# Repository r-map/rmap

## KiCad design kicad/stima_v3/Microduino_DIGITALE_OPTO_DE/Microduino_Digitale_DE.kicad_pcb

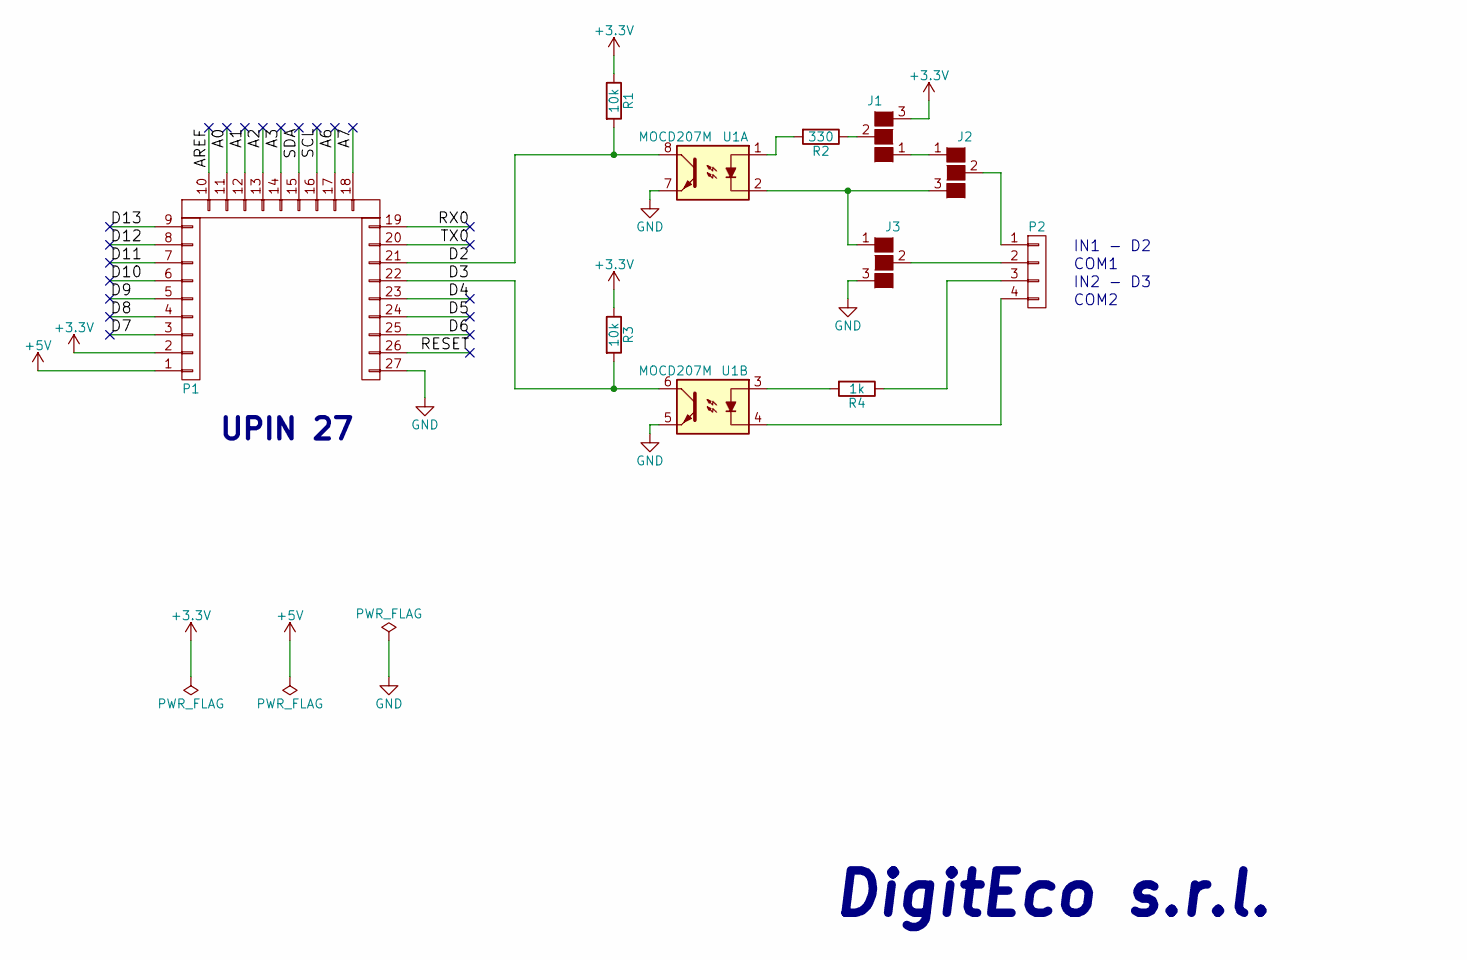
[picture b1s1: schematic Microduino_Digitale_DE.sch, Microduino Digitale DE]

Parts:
J1, J2, J3: GS3
P1: CONN_1x27; Upin_27
P2: CONN_01X04; WHURT_4pin_90°_61900411021
R1, R3: 10k; R_0805
R2: 330; R_0805
R4: 1k; R_0805
U1: MOCD207M; SOIC-8_3.9x4.9mm_Pitch1.27mm

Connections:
+3V3: J1.3 (G3), P1.2, R1.1, R3.1
+5V: P1.1
/A0: P1.11
/A1: P1.12
/A2: P1.13
/A3: P1.14
/A6: P1.17
/A7: P1.18
/AREF: P1.10
/D2: P1.21, R1.2, U1.8
/D3: P1.22, R3.2, U1.6
/D4: P1.23
/D5: P1.24
/D6: P1.25
/D7: P1.3
/D8: P1.4
/D9: P1.5
/D10: P1.6
/D11: P1.7
/D12: P1.8
/D13: P1.9
/RESET: P1.26
/RX0: P1.19
/SCL: P1.16
/SDA: P1.15
/TX0: P1.20
GND: J3.3 (G3), P1.27, U1.5, U1.7
unnamed: J1.1 (G1), J2.1 (G1)
unnamed: J1.2 (G2), R2.1
unnamed: J2.2 (G2), P2.1
unnamed: J2.3 (G3), J3.1 (G1), U1.2
unnamed: J3.2 (G2), P2.2
unnamed: P2.3, R4.1
unnamed: P2.4, U1.4
unnamed: R2.2, U1.1
unnamed: R4.2, U1.3

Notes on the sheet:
UPIN 27
DigitEco s.r.l.
COM2
IN2 - D3
COM1
IN1 - D2

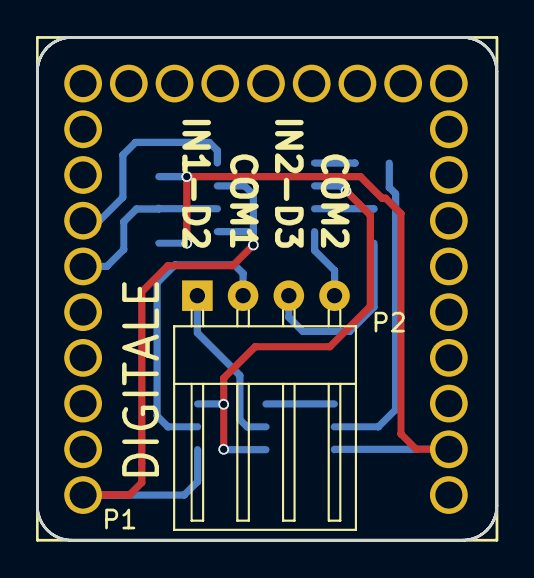
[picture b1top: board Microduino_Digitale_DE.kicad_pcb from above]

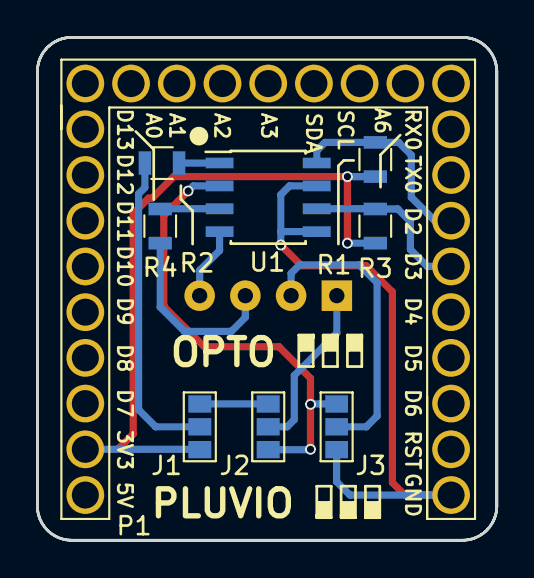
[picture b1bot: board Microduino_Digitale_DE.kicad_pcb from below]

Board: 2 copper layers, 25.5 x 27.9 mm, 10 parts (9 on the bottom side), 13 nets.

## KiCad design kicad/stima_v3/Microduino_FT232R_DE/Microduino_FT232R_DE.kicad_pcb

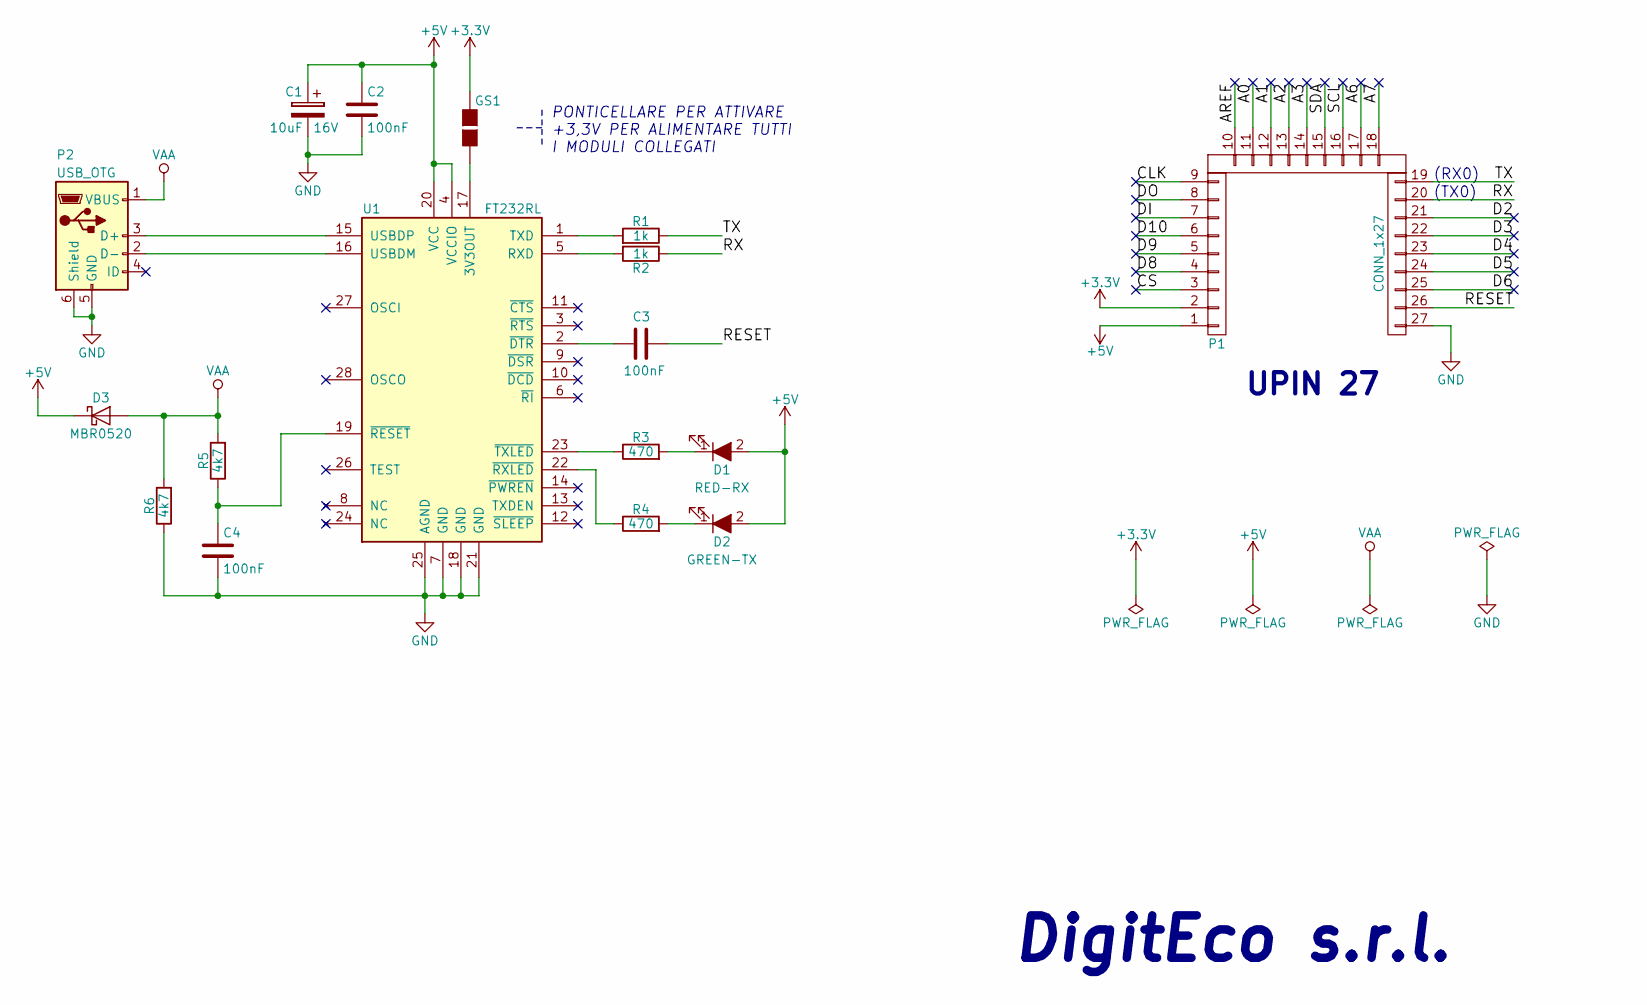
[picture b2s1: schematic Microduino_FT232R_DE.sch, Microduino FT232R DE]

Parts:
C1: 10uF; SMD-1210_Pol
C2, C3, C4: 100nF; C_0805
D1: RED-RX; LED_0805
D2: GREEN-TX; LED_0805
D3: MBR0520; D_SOD-123
GS1: GS2
P1: CONN_1x27; Upin_27
P2: USB_OTG; USB_Micro-B_Molex-105017-0001
R1, R2: 1k; R_0805
R3, R4: 470; R_0805
R5, R6: 4k7; R_0805
U1: FT232RL; SSOP-28_5.3x10.2mm_Pitch0.65mm

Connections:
+3V3: GS1.1 (G1), P1.2
+5V: C1.1, C2.1, D1.2 (A), D2.2 (A), D3.1 (K), P1.1, U1.4 (VCCIO), U1.20 (VCC)
/A0: P1.11
/A1: P1.12
/A2: P1.13
/A3: P1.14
/A6: P1.17
/A7: P1.18
/AREF: P1.10
/CLK: P1.9
/CS: P1.3
/D2: P1.21
/D3: P1.22
/D4: P1.23
/D5: P1.24
/D6: P1.25
/D8: P1.4
/D9: P1.5
/D10: P1.6
/DI: P1.7
/DO: P1.8
/RESET: C3.1, P1.26
/RX: P1.20, R2.1
/SCL: P1.16
/SDA: P1.15
/TX: P1.19, R1.1
GND: C1.2, C2.2, C4.2, P1.27, P2.5 (GND), P2.6 (Shield), R6.1, U1.7 (GND), U1.18 (GND), U1.21 (GND), U1.25 (AGND)
unnamed: C3.2, U1.2 (~DTR)
unnamed: C4.1, R5.1, U1.19 (~RESET)
unnamed: D1.1 (K), R3.2
unnamed: D2.1 (K), R4.2
unnamed: GS1.2 (G2), U1.17 (3V3OUT)
unnamed: P2.2 (D-), U1.16 (USBDM)
unnamed: P2.3 (D+), U1.15 (USBDP)
unnamed: R1.2, U1.1 (TXD)
unnamed: R2.2, U1.5 (RXD)
unnamed: R3.1, U1.23 (~TXLED)
unnamed: R4.1, U1.22 (~RXLED)
VAA: D3.2 (A), P2.1 (VBUS), R5.2, R6.2

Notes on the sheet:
UPIN 27
DigitEco s.r.l.
(RX0)
(TX0)
PONTICELLARE PER ATTIVARE +3,3V PER ALIMENTARE TUTTI I MODULI COLLEGATI

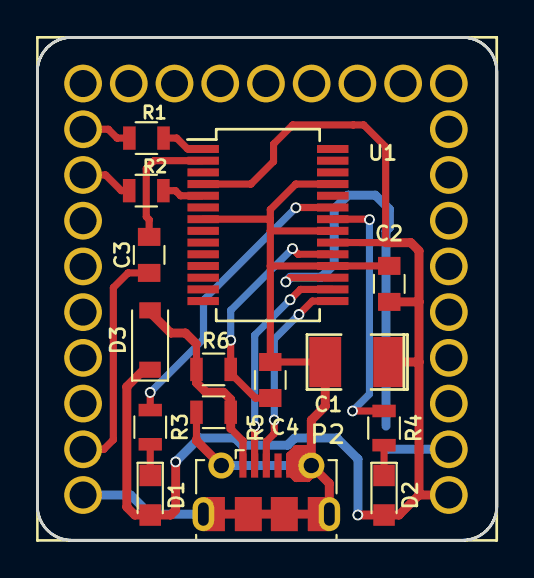
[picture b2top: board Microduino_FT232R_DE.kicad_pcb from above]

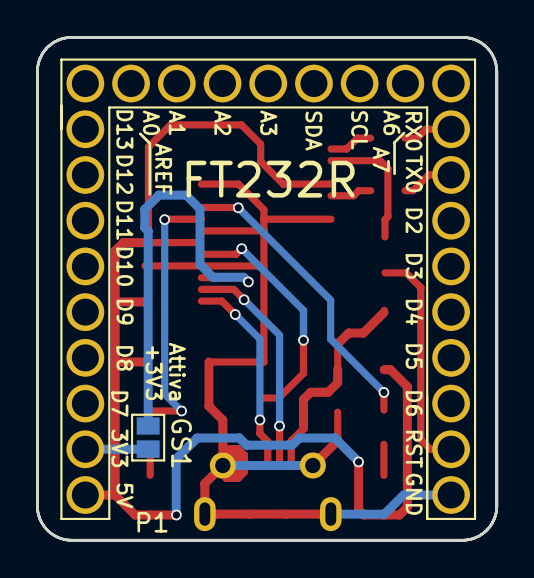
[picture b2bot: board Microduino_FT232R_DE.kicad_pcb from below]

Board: 2 copper layers, 25.5 x 27.9 mm, 17 parts (2 on the bottom side), 18 nets.

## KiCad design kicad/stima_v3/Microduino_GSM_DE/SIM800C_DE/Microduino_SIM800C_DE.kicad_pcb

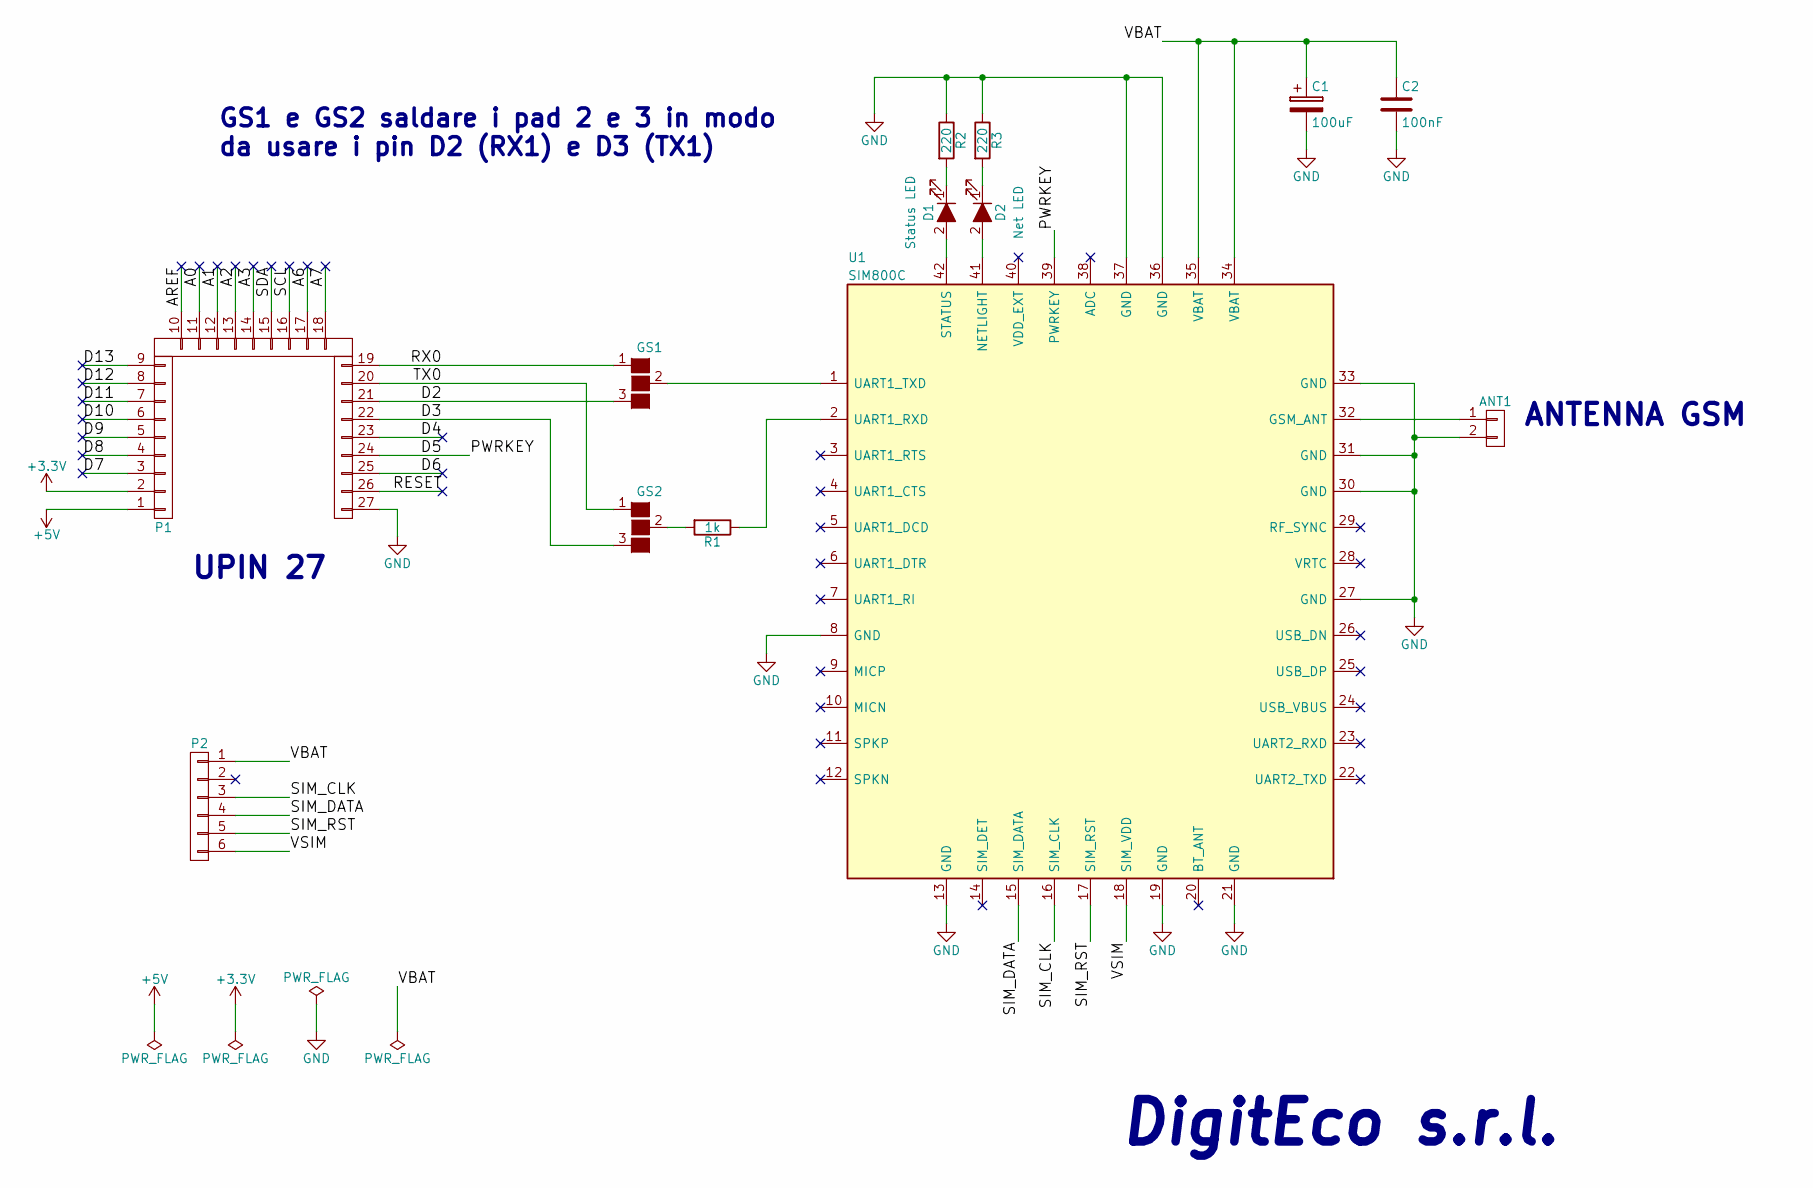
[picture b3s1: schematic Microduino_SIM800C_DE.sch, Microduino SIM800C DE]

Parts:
ANT1: CONN_01X02; Molex_SMA_Jack_Edge_Mount_microduino_2
C1: 100uF; CP_Tantalum_Case-B_EIA-3528-21_Reflow
C2: 100nF; C_0805
D1, D2: LED_ALT; LED_0805
GS1, GS2: GS3
P1: CONN_1x27; Upin_27
P2: CONN_01X06; Pin_Header_Straight_1x06_Pitch2.54mm
R1: 1k; R_0805
R2, R3: 220; R_0805
U1: SIM800C; SIM800C-42PIN

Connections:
+3V3: P1.2
+5V: P1.1
/A0: P1.11
/A1: P1.12
/A2: P1.13
/A3: P1.14
/A6: P1.17
/A7: P1.18
/AREF: P1.10
/D2: GS1.3 (G3), P1.21
/D3: GS2.3 (G3), P1.22
/D4: P1.23
/D5: P1.24, U1.39 (PWRKEY)
/D6: P1.25
/D7: P1.3
/D8: P1.4
/D9: P1.5
/D10: P1.6
/D11: P1.7
/D12: P1.8
/D13: P1.9
/RESET: P1.26
/RX0: GS1.1 (G1), P1.19
/SCL: P1.16
/SDA: P1.15
/SIM_CLK: P2.3, U1.16 (SIM_CLK)
/SIM_DATA: P2.4, U1.15 (SIM_DATA)
/SIM_RST: P2.5, U1.17 (SIM_RST)
/TX0: GS2.1 (G1), P1.20
/VBAT: C1.1, C2.1, P2.1, U1.34 (VBAT), U1.35 (VBAT)
/VSIM: P2.6, U1.18 (SIM_VDD)
GND: ANT1.2, C1.2, C2.2, P1.27, R2.1, R3.1, U1.8 (GND), U1.13 (GND), U1.19 (GND), U1.21 (GND), U1.27 (GND), U1.30 (GND), U1.31 (GND), U1.33 (GND), U1.36 (GND), U1.37 (GND)
unnamed: ANT1.1, U1.32 (GSM_ANT)
unnamed: D1.1 (K), R2.2
unnamed: D1.2 (A), U1.42 (STATUS)
unnamed: D2.1 (K), R3.2
unnamed: D2.2 (A), U1.41 (NETLIGHT)
unnamed: GS1.2 (G2), U1.1 (UART1_TXD)
unnamed: GS2.2 (G2), R1.2
unnamed: R1.1, U1.2 (UART1_RXD)

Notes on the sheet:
UPIN 27
DigitEco s.r.l.
ANTENNA GSM
GS1 e GS2 saldare i pad 2 e 3 in modo da usare i pin D2 (RX1) e D3 (TX1)

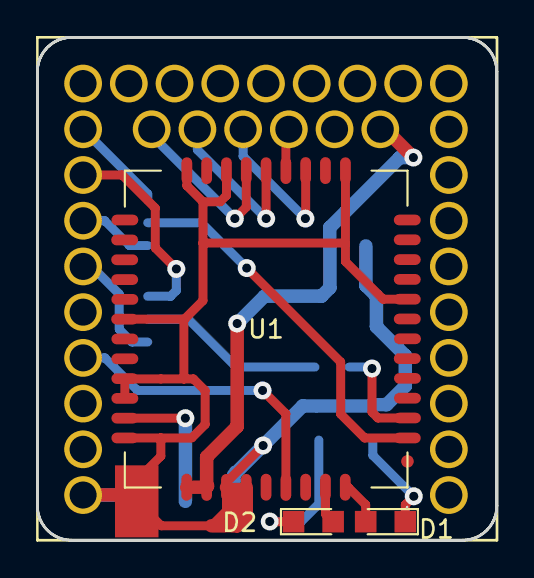
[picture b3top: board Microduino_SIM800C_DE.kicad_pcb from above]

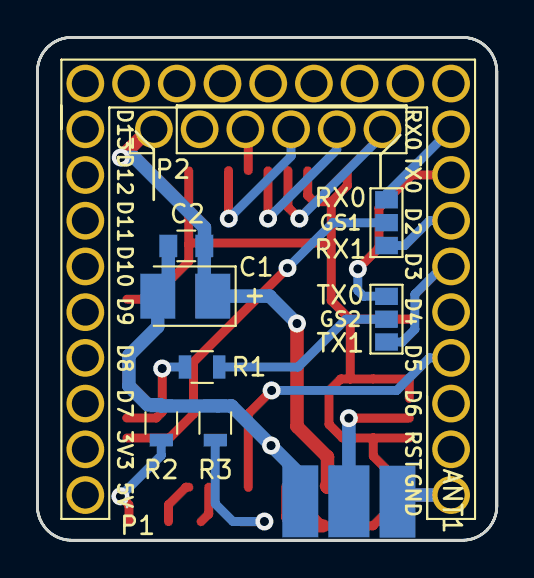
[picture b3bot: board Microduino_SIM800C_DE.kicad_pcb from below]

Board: 2 copper layers, 25.5 x 27.9 mm, 13 parts (10 on the bottom side), 19 nets.

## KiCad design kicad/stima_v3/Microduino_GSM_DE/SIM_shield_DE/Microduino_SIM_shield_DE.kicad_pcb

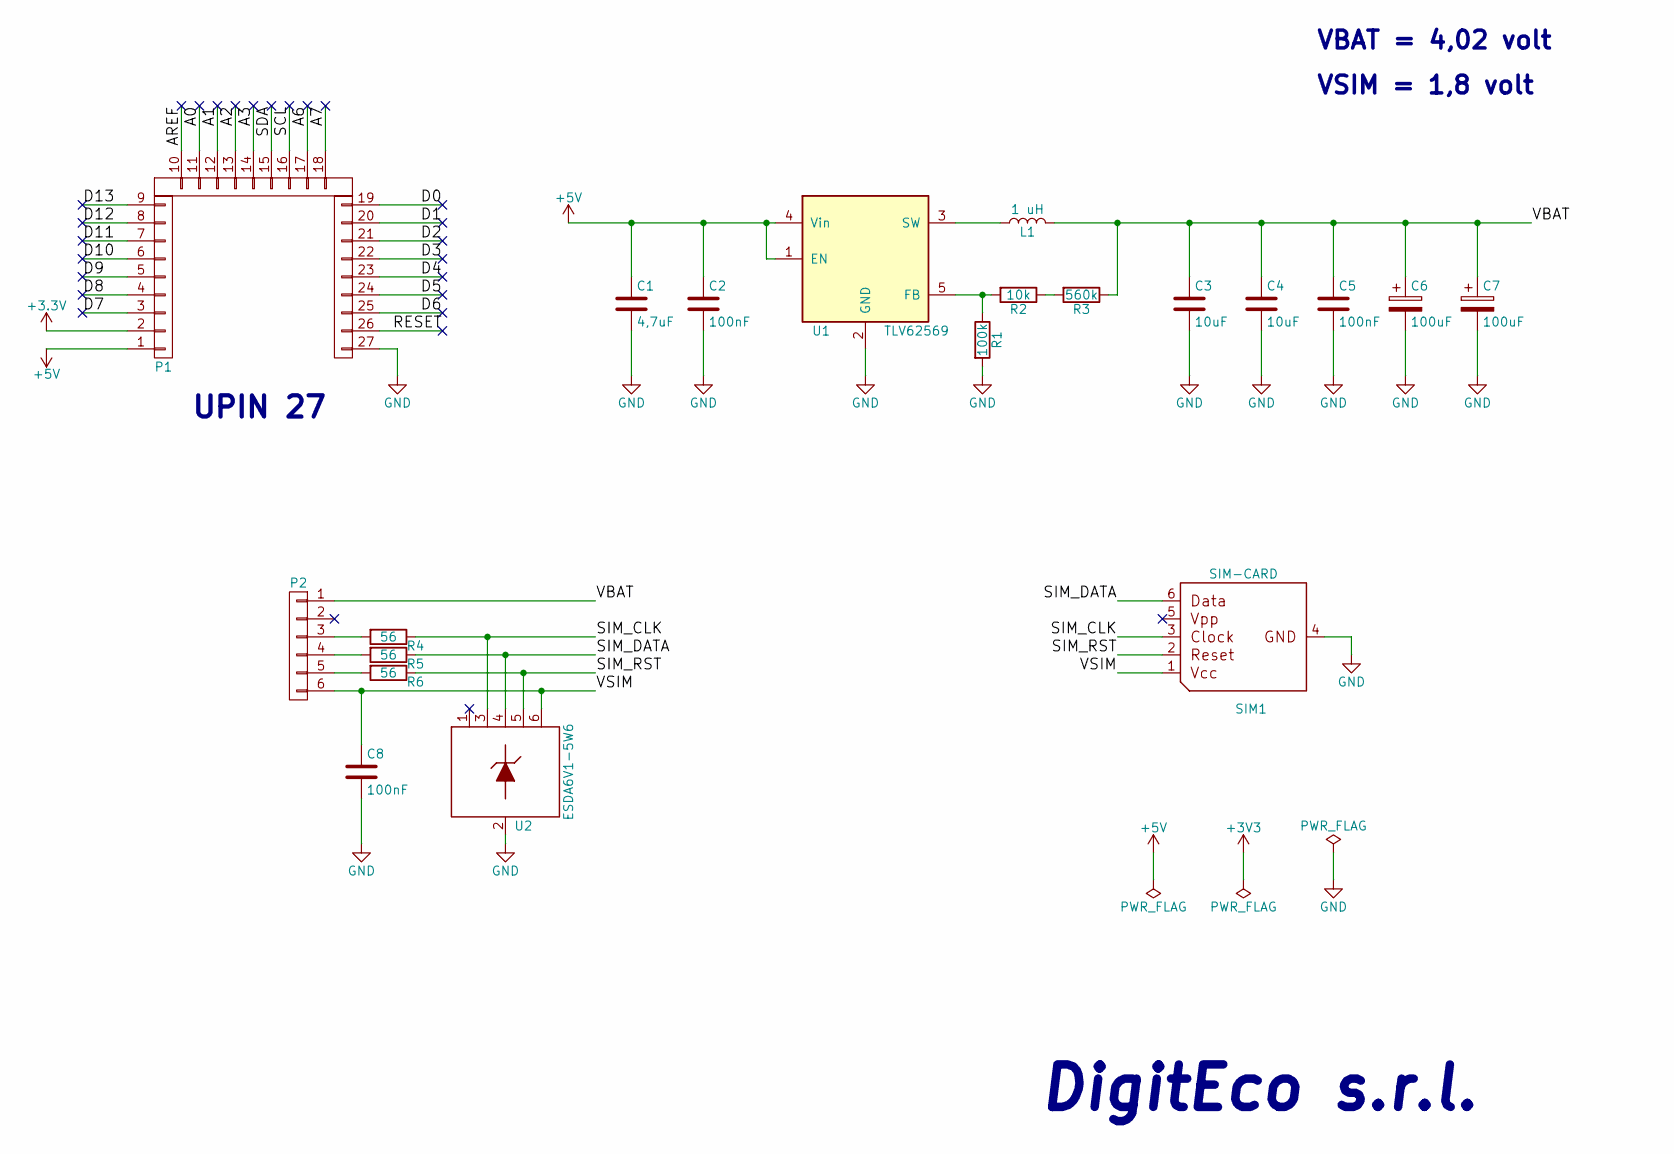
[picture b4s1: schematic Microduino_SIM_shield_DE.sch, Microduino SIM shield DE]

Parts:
C1: 4,7uF; C_0805
C2, C5, C8: 100nF; C_0805
C3, C4: 10uF; C_0805
C6, C7: 100uF; CP_Tantalum_Case-B_EIA-3528-21_Reflow
L1: 1 uH; Induttanza_SMD_3030_Vishay
P1: CONN_1x27; Upin_27
P2: CONN_01X06; Pin_Header_Straight_1x06_Pitch2.54mm
R1: 100k; R_0805
R2: 10k; R_0805
R3: 560k; R_0805
R4, R5, R6: 56; R_0805
SIM1: SIM-CARD; mini_sim_card_holder
U1: TLV62569; SOT-23-5
U2: ESDA6V1-5W6; SOT-363_SC-70-6

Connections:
+3V3: P1.2
+5V: C1.1, C2.1, P1.1, U1.1 (EN), U1.4 (Vin)
/A0: P1.11
/A1: P1.12
/A2: P1.13
/A3: P1.14
/A6: P1.17
/A7: P1.18
/AREF: P1.10
/D0: P1.19
/D1: P1.20
/D2: P1.21
/D3: P1.22
/D4: P1.23
/D5: P1.24
/D6: P1.25
/D7: P1.3
/D8: P1.4
/D9: P1.5
/D10: P1.6
/D11: P1.7
/D12: P1.8
/D13: P1.9
/RESET: P1.26
/SCL: P1.16
/SDA: P1.15
/SIM_CLK: R4.1, SIM1.3, U2.3
/SIM_DATA: R5.1, SIM1.6, U2.4
/SIM_RST: R6.1, SIM1.2, U2.5
/VBAT: C3.1, C4.1, C5.1, C6.1, C7.1, L1.2, P2.1, R3.1
/VSIM: C8.1, P2.6, SIM1.1, U2.6
GND: C1.2, C2.2, C3.2, C4.2, C5.2, C6.2, C7.2, C8.2, P1.27, R1.2, SIM1.4, U1.2 (GND), U2.2
unnamed: L1.1, U1.3 (SW)
unnamed: P2.3, R4.2
unnamed: P2.4, R5.2
unnamed: P2.5, R6.2
unnamed: R1.1, R2.2, U1.5 (FB)
unnamed: R2.1, R3.2

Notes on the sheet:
UPIN 27
DigitEco s.r.l.
VBAT = 4,02 volt
VSIM = 1,8 volt

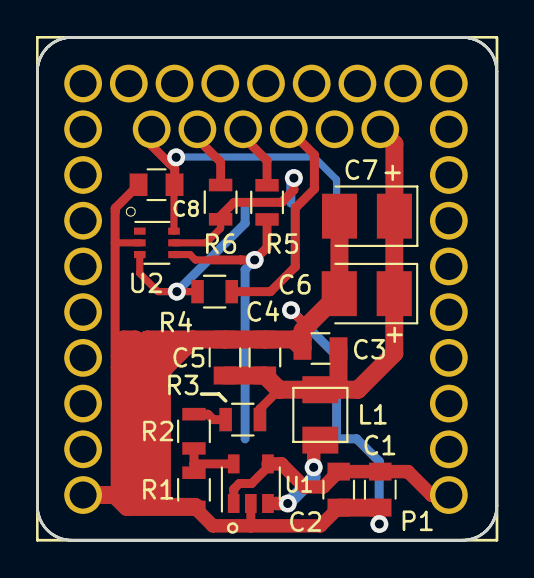
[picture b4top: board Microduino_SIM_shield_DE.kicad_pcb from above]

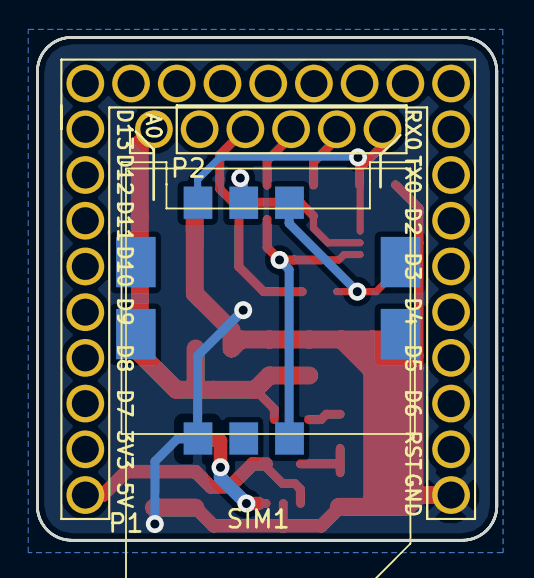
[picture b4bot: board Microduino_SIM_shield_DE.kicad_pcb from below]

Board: 2 copper layers, 25.5 x 27.9 mm, 20 parts (3 on the bottom side), 13 nets.

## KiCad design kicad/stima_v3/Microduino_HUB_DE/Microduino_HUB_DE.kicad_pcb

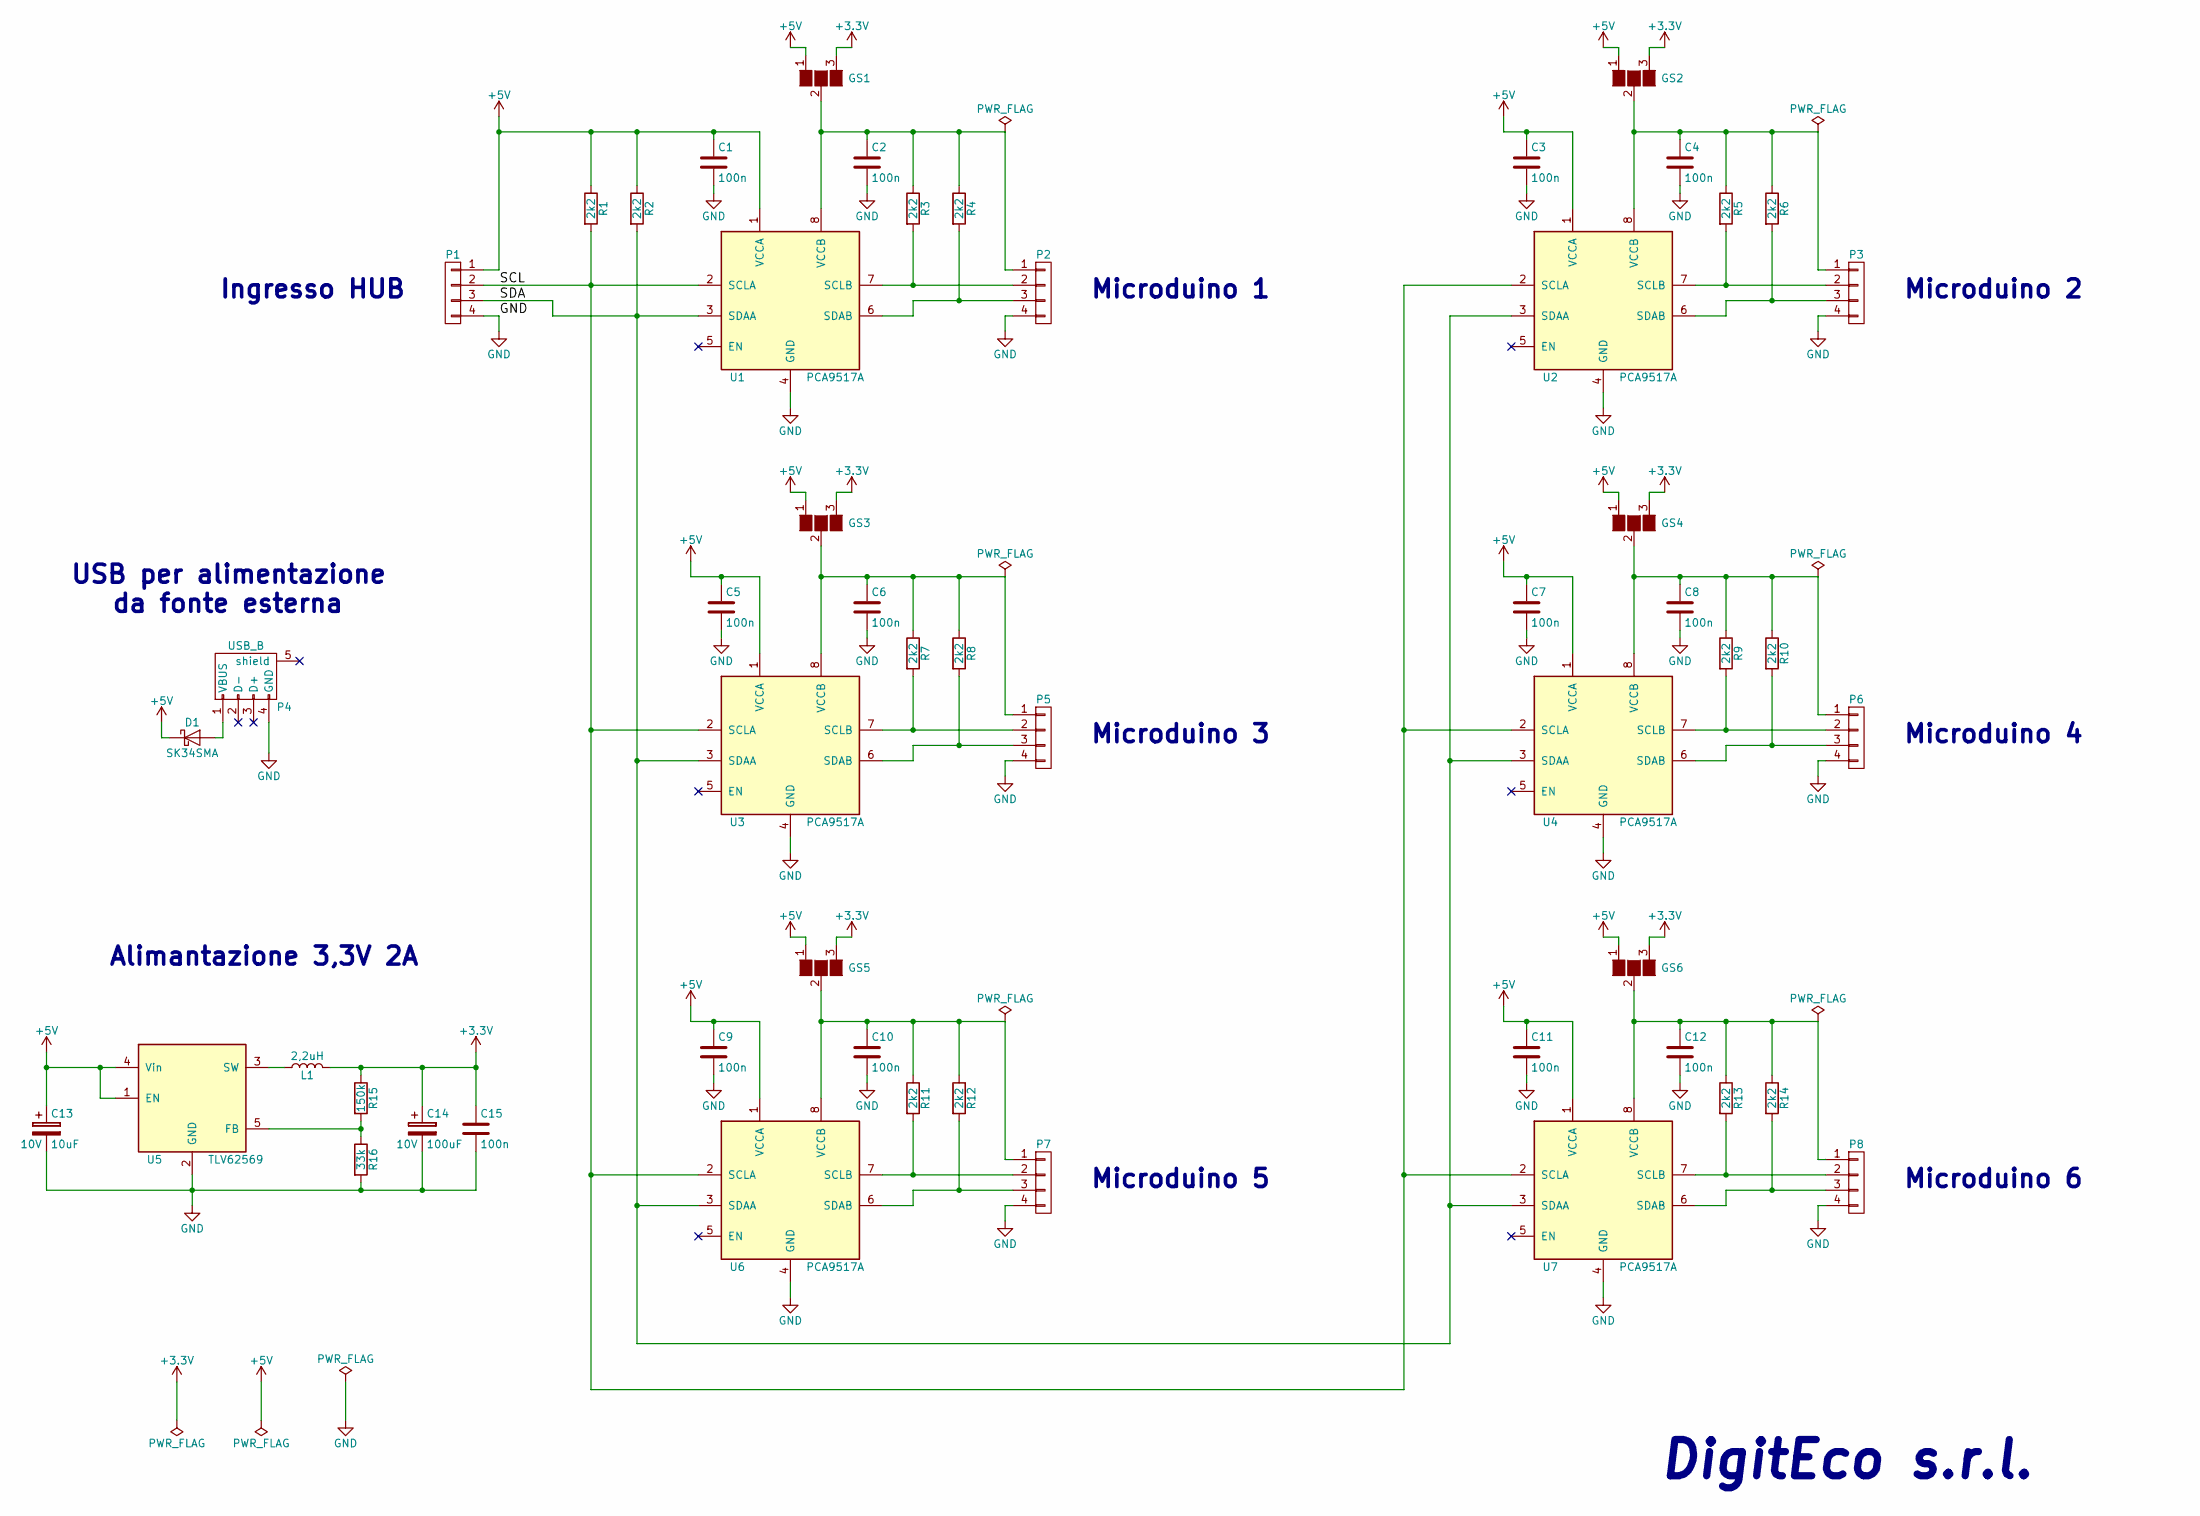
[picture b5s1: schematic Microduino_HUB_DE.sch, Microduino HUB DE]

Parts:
C1, C2, C3, C4, C5, C6, C7, C8, C9, C10, C11, C12, C15: 100n; C_1206
C13: 10uF; CP_Tantalum_Case-A_EIA-3216-18_Reflow
C14: 100uF; CP_Radial_D6.3mm_P2.50mm
D1: SK34SMA; D_SMA_Standard
GS1, GS2, GS3, GS4, GS5, GS6: GS3; Pin_Header_Straight_1x03_Pitch2.54mm
L1: 2,2uH; Induttanza_SMD_2520_Wurth
P1, P2, P3, P5, P6, P7, P8: CONN_01X04; WURTH_4pin_straight_61900411121
P4: USB_B
R1, R2, R3, R4, R5, R6, R7, R8, R9, R10, R11, R12, R13, R14: 2k2; R_1206
R15: 150k; R_1206
R16: 33k; R_1206
U1, U2, U3, U4, U6, U7: PCA9517A; SOIC-8_3.9x4.9mm_Pitch1.27mm
U5: TLV62569; SOT-23-5

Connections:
+3V3: C14.1, C15.1, GS1.3 (G3), GS2.3 (G3), GS3.3 (G3), GS4.3 (G3), GS5.3 (G3), GS6.3 (G3), L1.2, R15.1
+5V: C1.1, C3.1, C5.1, C7.1, C9.1, C11.1, C13.1, D1.1 (K), GS1.1 (G1), GS2.1 (G1), GS3.1 (G1), GS4.1 (G1), GS5.1 (G1), GS6.1 (G1), P1.1, R1.1, R2.1, U1.1 (VCCA), U2.1 (VCCA), U3.1 (VCCA), U4.1 (VCCA), U5.1 (EN), U5.4 (Vin), U6.1 (VCCA), U7.1 (VCCA)
/SCL: P1.2, R1.2, U1.2 (SCLA), U2.2 (SCLA), U3.2 (SCLA), U4.2 (SCLA), U6.2 (SCLA), U7.2 (SCLA)
/SDA: P1.3, R2.2, U1.3 (SDAA), U2.3 (SDAA), U3.3 (SDAA), U4.3 (SDAA), U6.3 (SDAA), U7.3 (SDAA)
GND: C1.2, C2.2, C3.2, C4.2, C5.2, C6.2, C7.2, C8.2, C9.2, C10.2, C11.2, C12.2, C13.2, C14.2, C15.2, P1.4, P2.4, P3.4, P4.4 (GND), P5.4, P6.4, P7.4, P8.4, R16.2, U1.4 (GND), U2.4 (GND), U3.4 (GND), U4.4 (GND), U5.2 (GND), U6.4 (GND), U7.4 (GND)
unnamed: C2.1, GS1.2 (G2), P2.1, R3.1, R4.1, U1.8 (VCCB)
unnamed: C4.1, GS2.2 (G2), P3.1, R5.1, R6.1, U2.8 (VCCB)
unnamed: C6.1, GS3.2 (G2), P5.1, R7.1, R8.1, U3.8 (VCCB)
unnamed: C8.1, GS4.2 (G2), P6.1, R9.1, R10.1, U4.8 (VCCB)
unnamed: C10.1, GS5.2 (G2), P7.1, R11.1, R12.1, U6.8 (VCCB)
unnamed: C12.1, GS6.2 (G2), P8.1, R13.1, R14.1, U7.8 (VCCB)
unnamed: D1.2 (A), P4.1 (VBUS)
unnamed: L1.1, U5.3 (SW)
unnamed: P2.2, R3.2, U1.7 (SCLB)
unnamed: P2.3, R4.2, U1.6 (SDAB)
unnamed: P3.2, R5.2, U2.7 (SCLB)
unnamed: P3.3, R6.2, U2.6 (SDAB)
unnamed: P5.2, R7.2, U3.7 (SCLB)
unnamed: P5.3, R8.2, U3.6 (SDAB)
unnamed: P6.2, R9.2, U4.7 (SCLB)
unnamed: P6.3, R10.2, U4.6 (SDAB)
unnamed: P7.2, R11.2, U6.7 (SCLB)
unnamed: P7.3, R12.2, U6.6 (SDAB)
unnamed: P8.2, R13.2, U7.7 (SCLB)
unnamed: P8.3, R14.2, U7.6 (SDAB)
unnamed: R15.2, R16.1, U5.5 (FB)

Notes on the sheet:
DigitEco s.r.l.
Microduino 1
Microduino 3
Microduino 5
Microduino 2
Microduino 4
Microduino 6
Ingresso HUB
USB per alimentazione da fonte esterna
Alimantazione 3,3V 2A

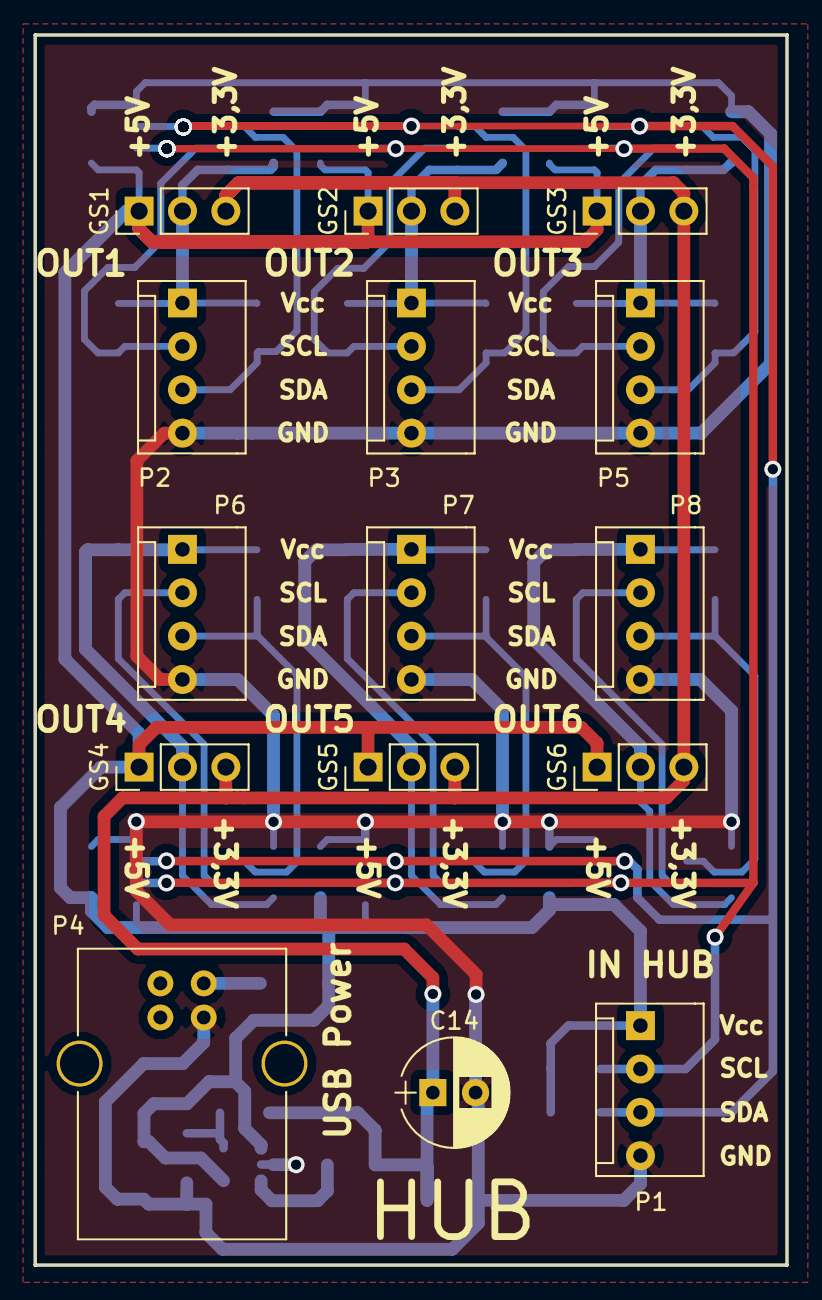
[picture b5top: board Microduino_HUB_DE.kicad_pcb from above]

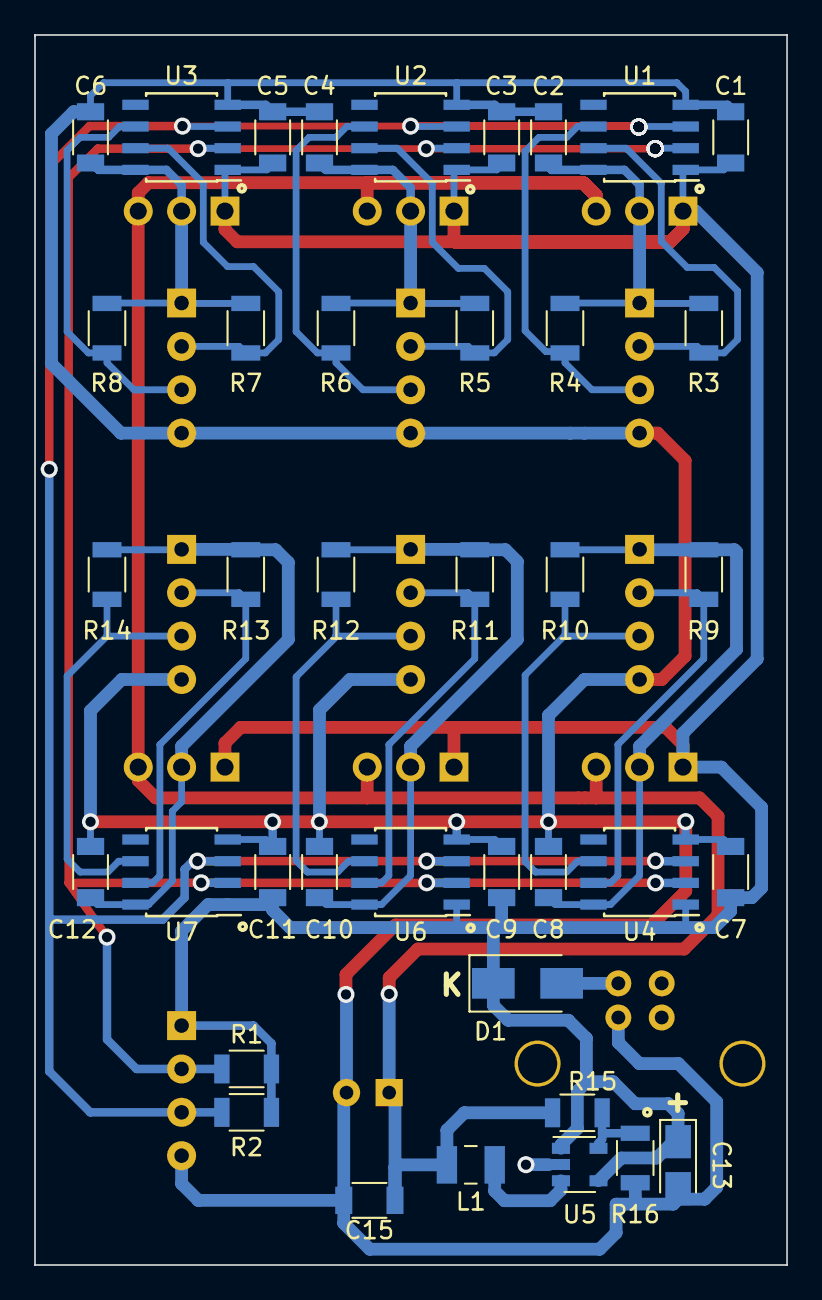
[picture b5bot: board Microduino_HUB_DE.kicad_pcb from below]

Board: 2 copper layers, 44.0 x 72.0 mm, 54 parts (39 on the bottom side), 26 nets.

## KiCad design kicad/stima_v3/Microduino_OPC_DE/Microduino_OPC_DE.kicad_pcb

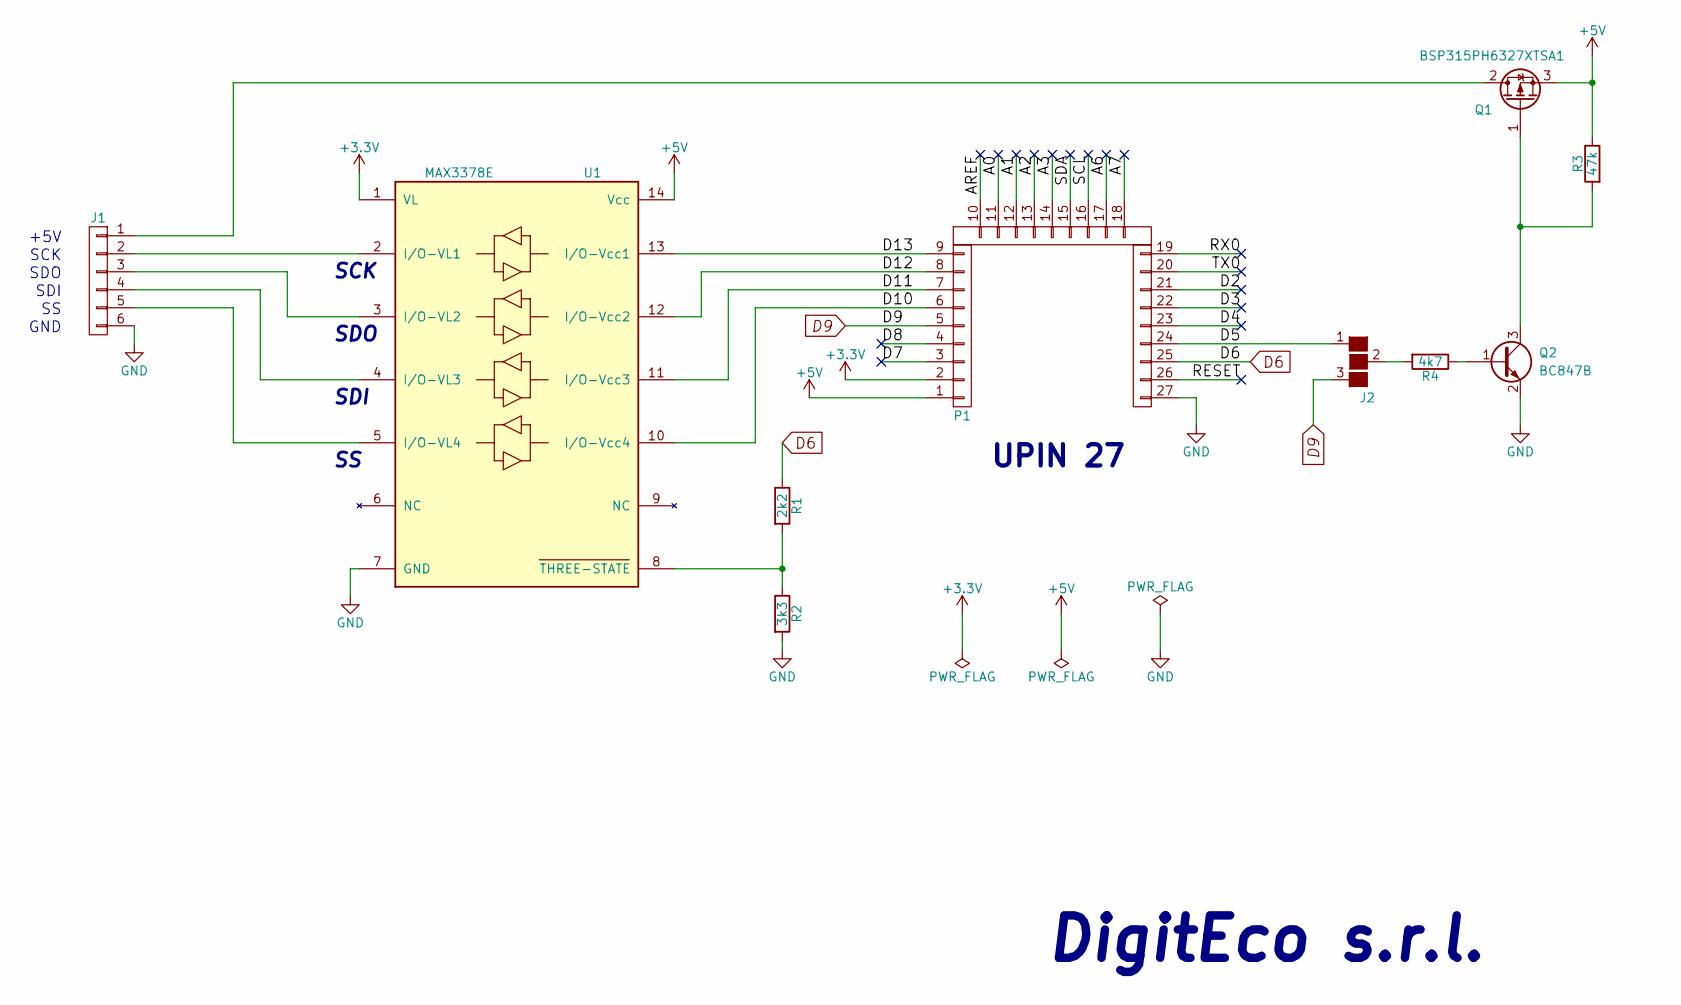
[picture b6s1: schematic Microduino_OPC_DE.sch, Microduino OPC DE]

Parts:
J1: CONN_01X06; Molex_PicoClasp_501568-0607_1x06_P1.0mm_Orizzontal
J2: GS3
P1: CONN_1x27; Upin_27
Q1: BSP315PH6327XTSA1; SOT-223-3_TabPin2
Q2: BC847B; SOT-23
R1: 2k2; R_0805
R2: 3k3; R_0805
R3: 47k; R_0805
R4: 4k7; R_0805
U1: MAX3378E; TSSOP-14_4.4x5mm_Pitch0.65mm

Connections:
+3V3: P1.2, U1.1 (VL)
+5V: P1.1, Q1.3 (S), R3.1, U1.14 (Vcc)
/A0: P1.11
/A1: P1.12
/A2: P1.13
/A3: P1.14
/A6: P1.17
/A7: P1.18
/AREF: P1.10
/D2: P1.21
/D3: P1.22
/D4: P1.23
/D5: J2.1 (G1), P1.24
/D7: P1.3
/D8: P1.4
/D10: P1.6, U1.10 (I/O-Vcc4)
/D11: P1.7, U1.11 (I/O-Vcc3)
/D12: P1.8, U1.12 (I/O-Vcc2)
/D13: P1.9, U1.13 (I/O-Vcc1)
/RESET: P1.26
/RX0: P1.19
/SCL: P1.16
/SDA: P1.15
/TX0: P1.20
D6: P1.25, R1.1
D9: J2.3 (G3), P1.5
GND: J1.6, P1.27, Q2.2 (E), R2.2, U1.7 (GND)
unnamed: J1.1, Q1.2 (D)
unnamed: J1.2, U1.2 (I/O-VL1)
unnamed: J1.3, U1.3 (I/O-VL2)
unnamed: J1.4, U1.4 (I/O-VL3)
unnamed: J1.5, U1.5 (I/O-VL4)
unnamed: J2.2 (G2), R4.2
unnamed: Q1.1 (G), Q2.3 (C), R3.2
unnamed: Q2.1 (B), R4.1
unnamed: R1.2, R2.1, U1.8 (THREE-STATE)

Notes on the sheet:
UPIN 27
DigitEco s.r.l.
SDI
SDO
SCK
+5V
GND
